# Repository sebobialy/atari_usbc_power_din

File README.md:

# Introduction

This is a simple power DIN connector USB-C replacement for Atari 8-bit computers, with PowerDelivery capability.

# Options

## Simple

* PCB
* USB-C connector
* Jumper over fuse

This configuration will work with dumb chargers that do not care about PD. Should work also with USB-C<>USB-A cables.

## Advanced

* PCB
* USB-C connector
* IP2721
* 5.1kOhm resistors
* Jumper over fuse

This configuration will work with all PowerDelivery chargers, via USB-C<>UAB-C cables. Should work with power banks, phone chargers, laptop chargers, etc.

## Ultimate

* PCB
* USB-C connector
* IP2721
* 5.1kOhm resistors
* 10nF capacitor
* 5.6V zener diode around 5W
* Polyfuse 1-2A.

This configuration will work with all chargers and additionally protect your hardware from reversed polarity or overvoltage, just in case.

# PCB

PCB was designed using KiCAD. All components are 0805 in size.

# Stand

To properly mount this DIN replacement, you need to print a small stand, using any 3D printer. OpenSCAD file is provided. Please install OpenSCAD, load the design file, press F6, and export STL for printing. You will also need some wires to solder it, trough the stand.

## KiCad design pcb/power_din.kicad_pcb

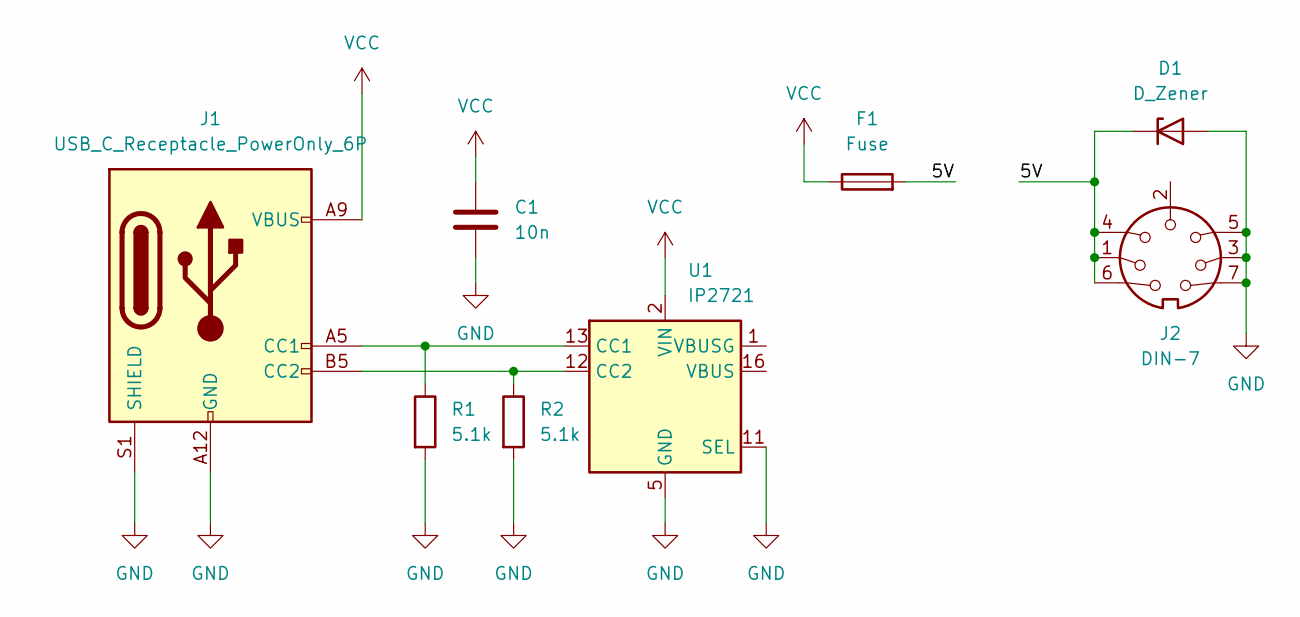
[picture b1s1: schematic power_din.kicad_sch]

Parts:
C1: 10n; C_0805_2012Metric
D1: D_Zener; D_T-1_P5.08mm_Horizontal
F1: Fuse; Fuse_0805_2012Metric
J1: USB_C_Receptacle_PowerOnly_6P; USB_C_Receptacle_GCT_USB4125-xx-x_6P_TopMnt_Horizontal
J2: DIN-7; din7_fake
R1, R2: 5.1k; R_0805_2012Metric
U1: IP2721; TSSOP-16_4.4x5mm_P0.65mm

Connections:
/5V: D1.1 (K), F1.2, J2.1, J2.4, J2.6
GND: C1.2, D1.2 (A), J1.A12 (GND), J1.B12 (GND), J1.S1 (SHIELD), J2.3, J2.5, J2.7, R1.2, R2.2, U1.5 (GND), U1.11 (SEL)
unnamed: J1.A5 (CC1), R1.1, U1.13 (CC1)
unnamed: J1.B5 (CC2), R2.1, U1.12 (CC2)
VCC: C1.1, F1.1, J1.A9 (VBUS), J1.B9 (VBUS), U1.2 (VIN)

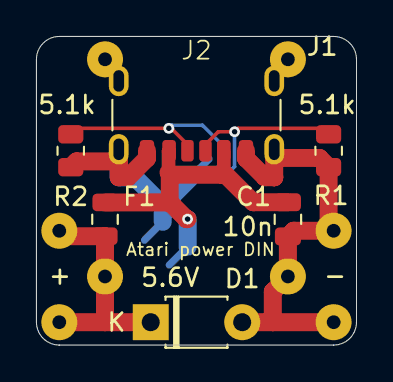
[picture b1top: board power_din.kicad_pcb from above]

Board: 2 copper layers, 17.8 x 17.1 mm, 8 parts (1 on the bottom side), 5 nets.

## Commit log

2024-08-24 images
2024-08-24 readme update
2024-08-24 stand
2024-08-24 production files
